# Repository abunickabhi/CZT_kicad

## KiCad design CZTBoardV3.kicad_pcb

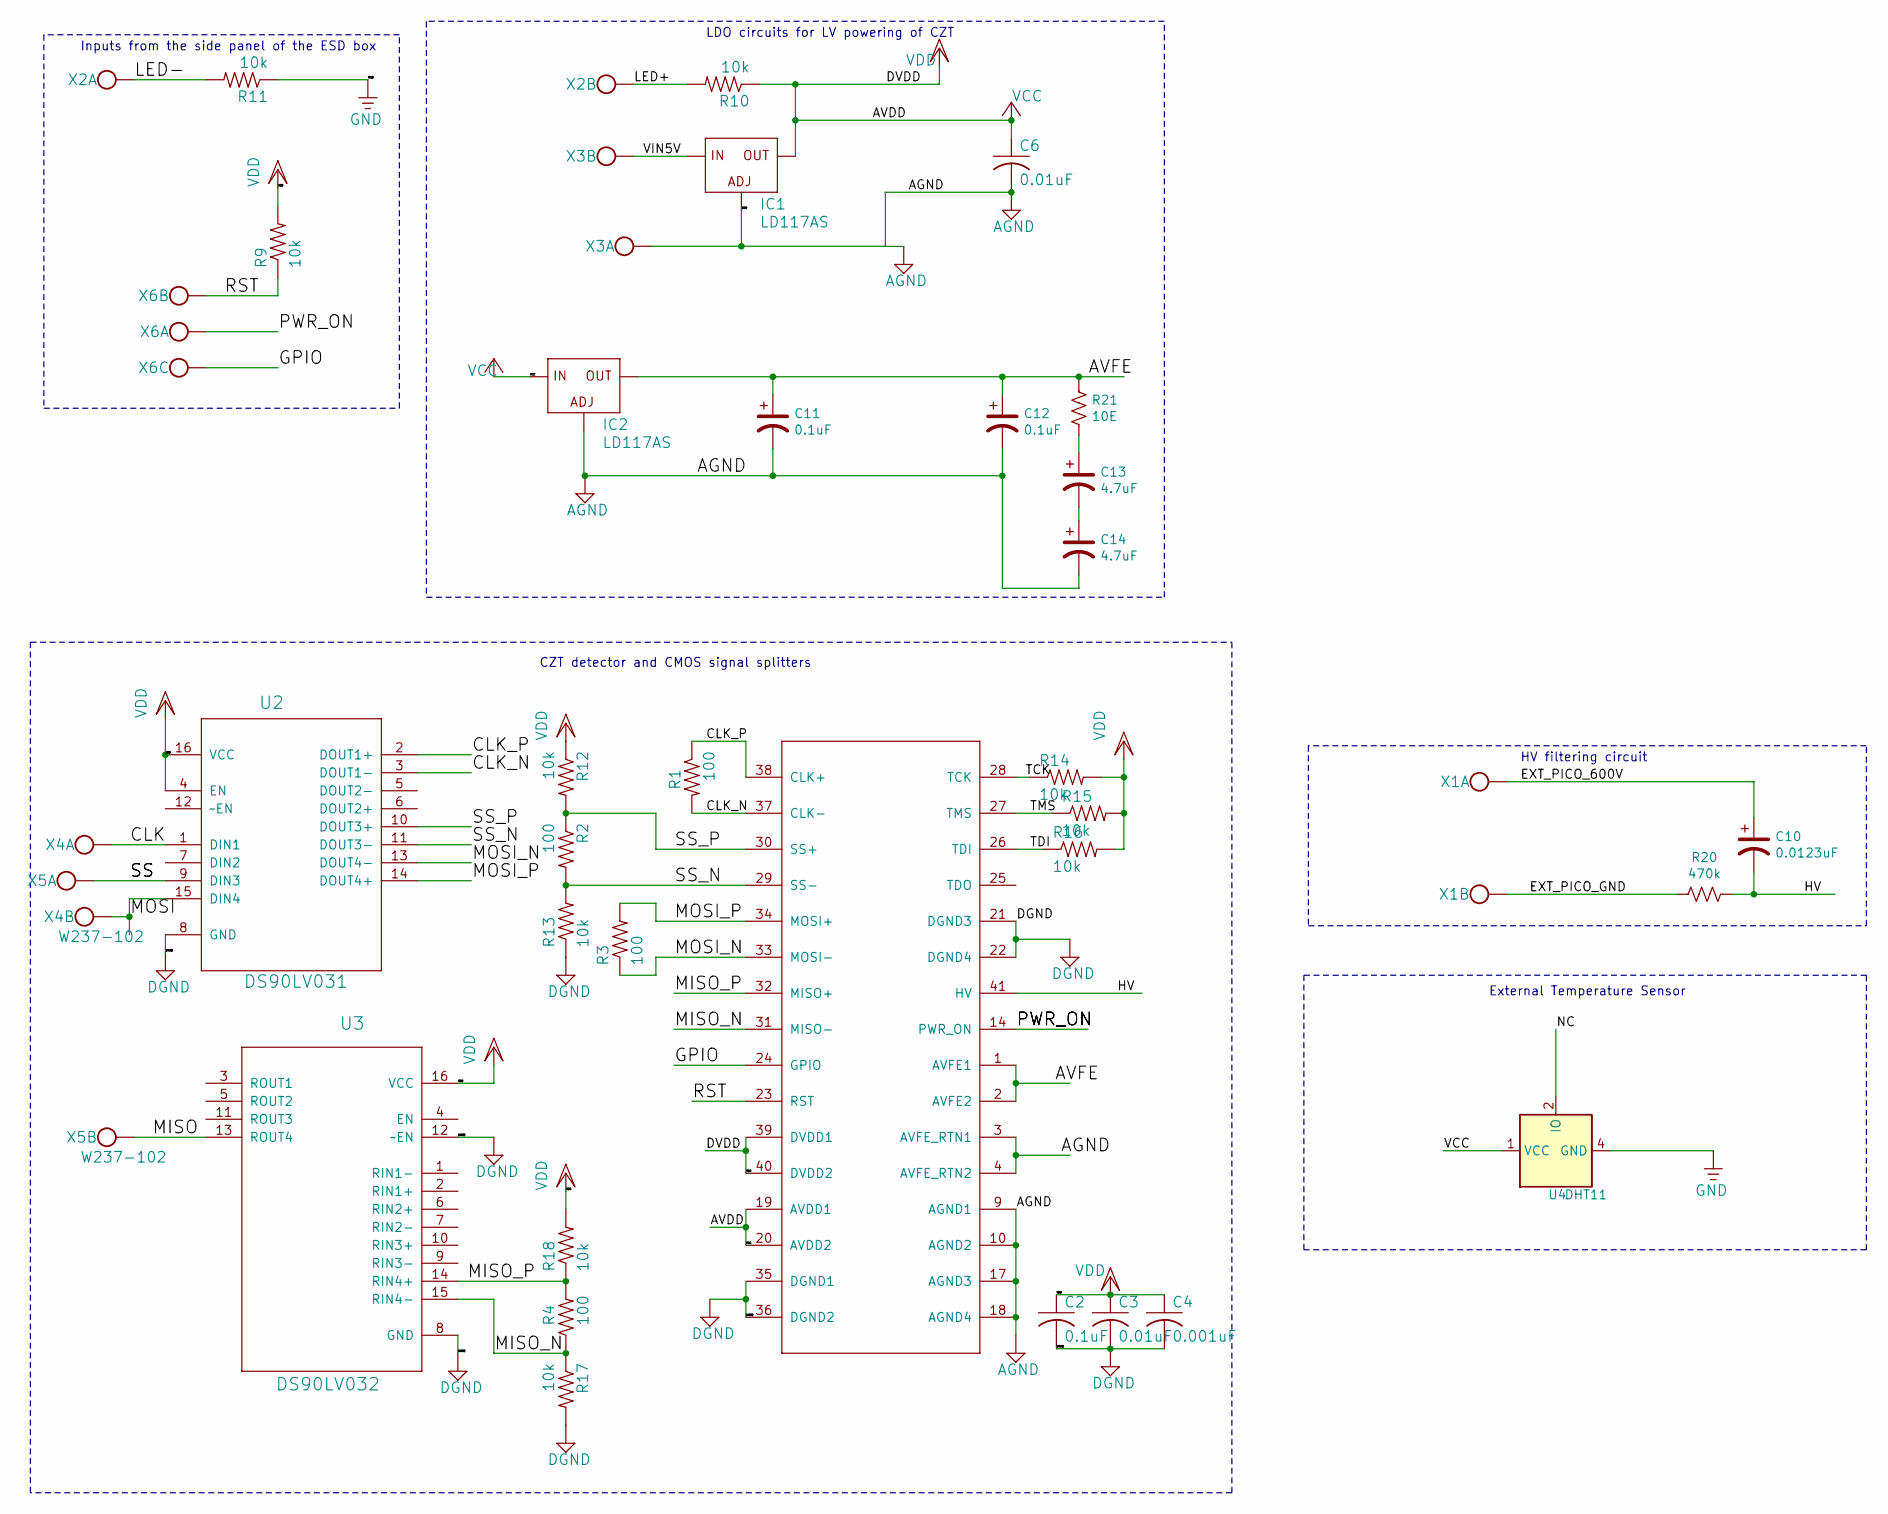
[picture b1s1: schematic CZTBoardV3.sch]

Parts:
C2, C11, C12: 0.1uF; C0805K
C3, C6: 0.01uF; C0805K
C4: 0.001uF; C0805K
C10: 0.0123uF; C0805K
C13, C14: 4.7uF; C0805K
IC1, IC2: LD117AS; SOT223
R1, R2, R3, R4: 100; R1206
R9, R10, R11, R12, R13, R14, R15, R16, R17, R18: 10k; R1206
R20: 470k; R1206
R21: 10E; R1206
U1: ORBOTECH_OMS40G256
U2: DS90LV031; SOIC127P600X175-16N
U3: DS90LV032; SOIC127P600X175-16N
U4: DHT11; Aosong_DHT11_5.5x12.0_P2.54mm
X1, X2, X3, X4, X5: W237-102
X6: W237-103

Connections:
/AVFE: C11.1, C12.1, IC2.4 (OUT), R21.1, U1.1 (AVFE1), U1.2 (AVFE2)
/CLK: U2.1 (DIN1), X4.1
/CLK_N: R1.2, U1.37 (CLK-), U2.3 (DOUT1-)
/CLK_P: R1.1, U1.38 (CLK+), U2.2 (DOUT1+)
/EXT_PICO_600V: C10.1, X1.1
/EXT_PICO_GND: R20.1, X1.2
/GPIO: U1.24 (GPIO), X6.3
/HV: C10.2, R20.2, U1.41 (HV)
/LED+: R10.2, X2.2
/LED-: R11.2, X2.1
/MISO: U3.13 (ROUT4), X5.2
/MISO_N: R4.1, R17.1, U1.31 (MISO-), U3.15 (RIN4-)
/MISO_P: R4.2, R18.1, U1.32 (MISO+), U3.14 (RIN4+)
/MOSI: U2.15 (DIN4), X4.2
/MOSI_N: R3.1, U1.33 (MOSI-), U2.13 (DOUT4-)
/MOSI_P: R3.2, U1.34 (MOSI+), U2.14 (DOUT4+)
/NC: U4.2 (IO)
/PWR_ON: U1.14 (PWR_ON), X6.1
/RST: R9.1, U1.23 (RST), X6.2
/SS: U2.9 (DIN3), X5.1
/SS_N: R2.2, R13.2, U1.29 (SS-), U2.11 (DOUT3-)
/SS_P: R2.1, R12.2, U1.30 (SS+), U2.10 (DOUT3+)
/TCK: R14.1, U1.28 (TCK)
/TDI: R16.1, U1.26 (TDI)
/TMS: R15.1, U1.27 (TMS)
/VIN5V: IC1.3 (IN), X3.2
AGND: C6.2, C11.2, C12.2, C14.2, IC1.1 (ADJ), IC2.1 (ADJ), R11.1, U1.3 (AVFE_RTN1), U1.4 (AVFE_RTN2), U1.9 (AGND1), U1.10 (AGND2), U1.17 (AGND3), U1.18 (AGND4), U4.4 (GND), X3.1
DGND: C2.2, C3.2, C4.2, R13.1, R17.2, U1.21 (DGND3), U1.22 (DGND4), U1.35 (DGND1), U1.36 (DGND2), U2.8 (GND), U3.8 (GND), U3.12 (~~EN)
unnamed: C13.1, R21.2
unnamed: C13.2, C14.1
VCC: C2.1, C3.1, C4.1, C6.1, IC1.4 (OUT), IC2.3 (IN), R9.2, R10.1, R12.1, R14.2, R15.2, R16.2, R18.2, U1.19 (AVDD1), U1.20 (AVDD2), U1.39 (DVDD1), U1.40 (DVDD2), U2.4 (EN), U2.16 (VCC), U3.16 (VCC), U4.1 (VCC)

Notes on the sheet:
CZT detector and CMOS signal splitters
Inputs from the side panel of the ESD box
LDO circuits for LV powering of CZT
HV filtering circuit
External Temperature Sensor

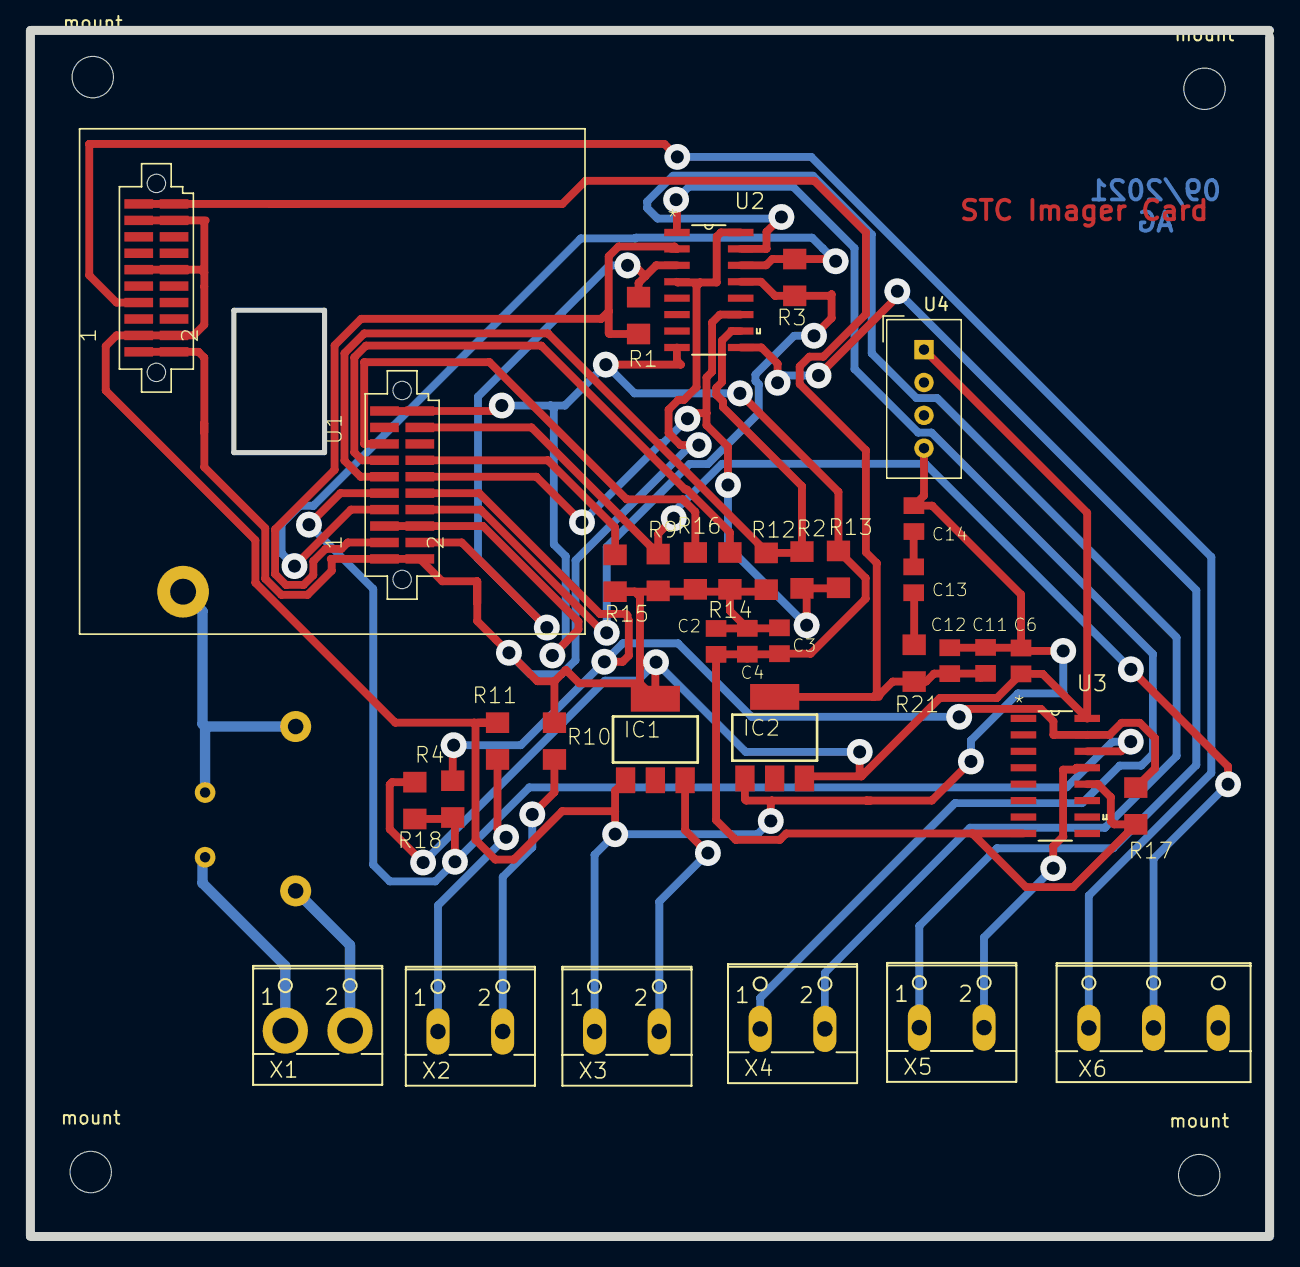
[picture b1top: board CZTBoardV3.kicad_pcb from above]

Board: 2 copper layers, 95.8 x 93.2 mm, 41 parts (0 on the bottom side), 30 nets.

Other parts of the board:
mount: MountingHole_3.2mm_M3
mount#2, mount#3, mount#4: MountingHole_3.2mm_M3

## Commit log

2021-08-10 kicad design
2021-08-10 changes to temperature sensor connection
2021-08-23 new layout
2021-08-24 added side panel
2021-08-24 airwire removal time
2021-08-25 nearing completion
2021-08-25 push
2021-08-26 simplistic design
2021-08-27 half routing done
2021-08-27 layout done
2021-08-30 gerbers included
2021-09-13 final gerbers with drill files generated as well
2021-09-13 changes to make directory clean
2021-09-29 some changes from pcbpower
2021-10-20 git issue
